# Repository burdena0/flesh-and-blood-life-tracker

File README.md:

# Flesh and Blood Life Tracker

A two-player life and resource counter for Flesh and Blood. This repo contains the compact E1 version: ESP32-S3 firmware, a KiCad carrier board, and host tests. It supports 20 or 40 starting life, undo, reset confirmation, and resource tracking. It can also serve as a general tabletop counter; no game artwork or logos are included.

## Current hardware and firmware

- ESP32-S3-Zero module, native ESP-IDF/FreeRTOS through PlatformIO.
- CL3641AH four-digit common-cathode display and SN74HC595 shift register.
- Debounced button events, state ownership, multiplexed display updates and resource LEDs.
- 70 x 80 mm two-layer KiCad carrier board with editable schematic, footprints and BOM.
- Host tests for game-state and shift-register behavior.

Read `README.txt` for the exact GPIO map, parts and assembly instructions. Build from
`firmware` with PlatformIO. Host test sources and CMake configuration are in
`firmware/tests`. The complete original workspace also contains historical Pico,
normal-ESP32 and older carrier variants; they are intentionally not mixed into this
current revision snapshot. Paths in historical prose may refer to those excluded
variants. Do not substitute their pin maps for the compact S3 board.

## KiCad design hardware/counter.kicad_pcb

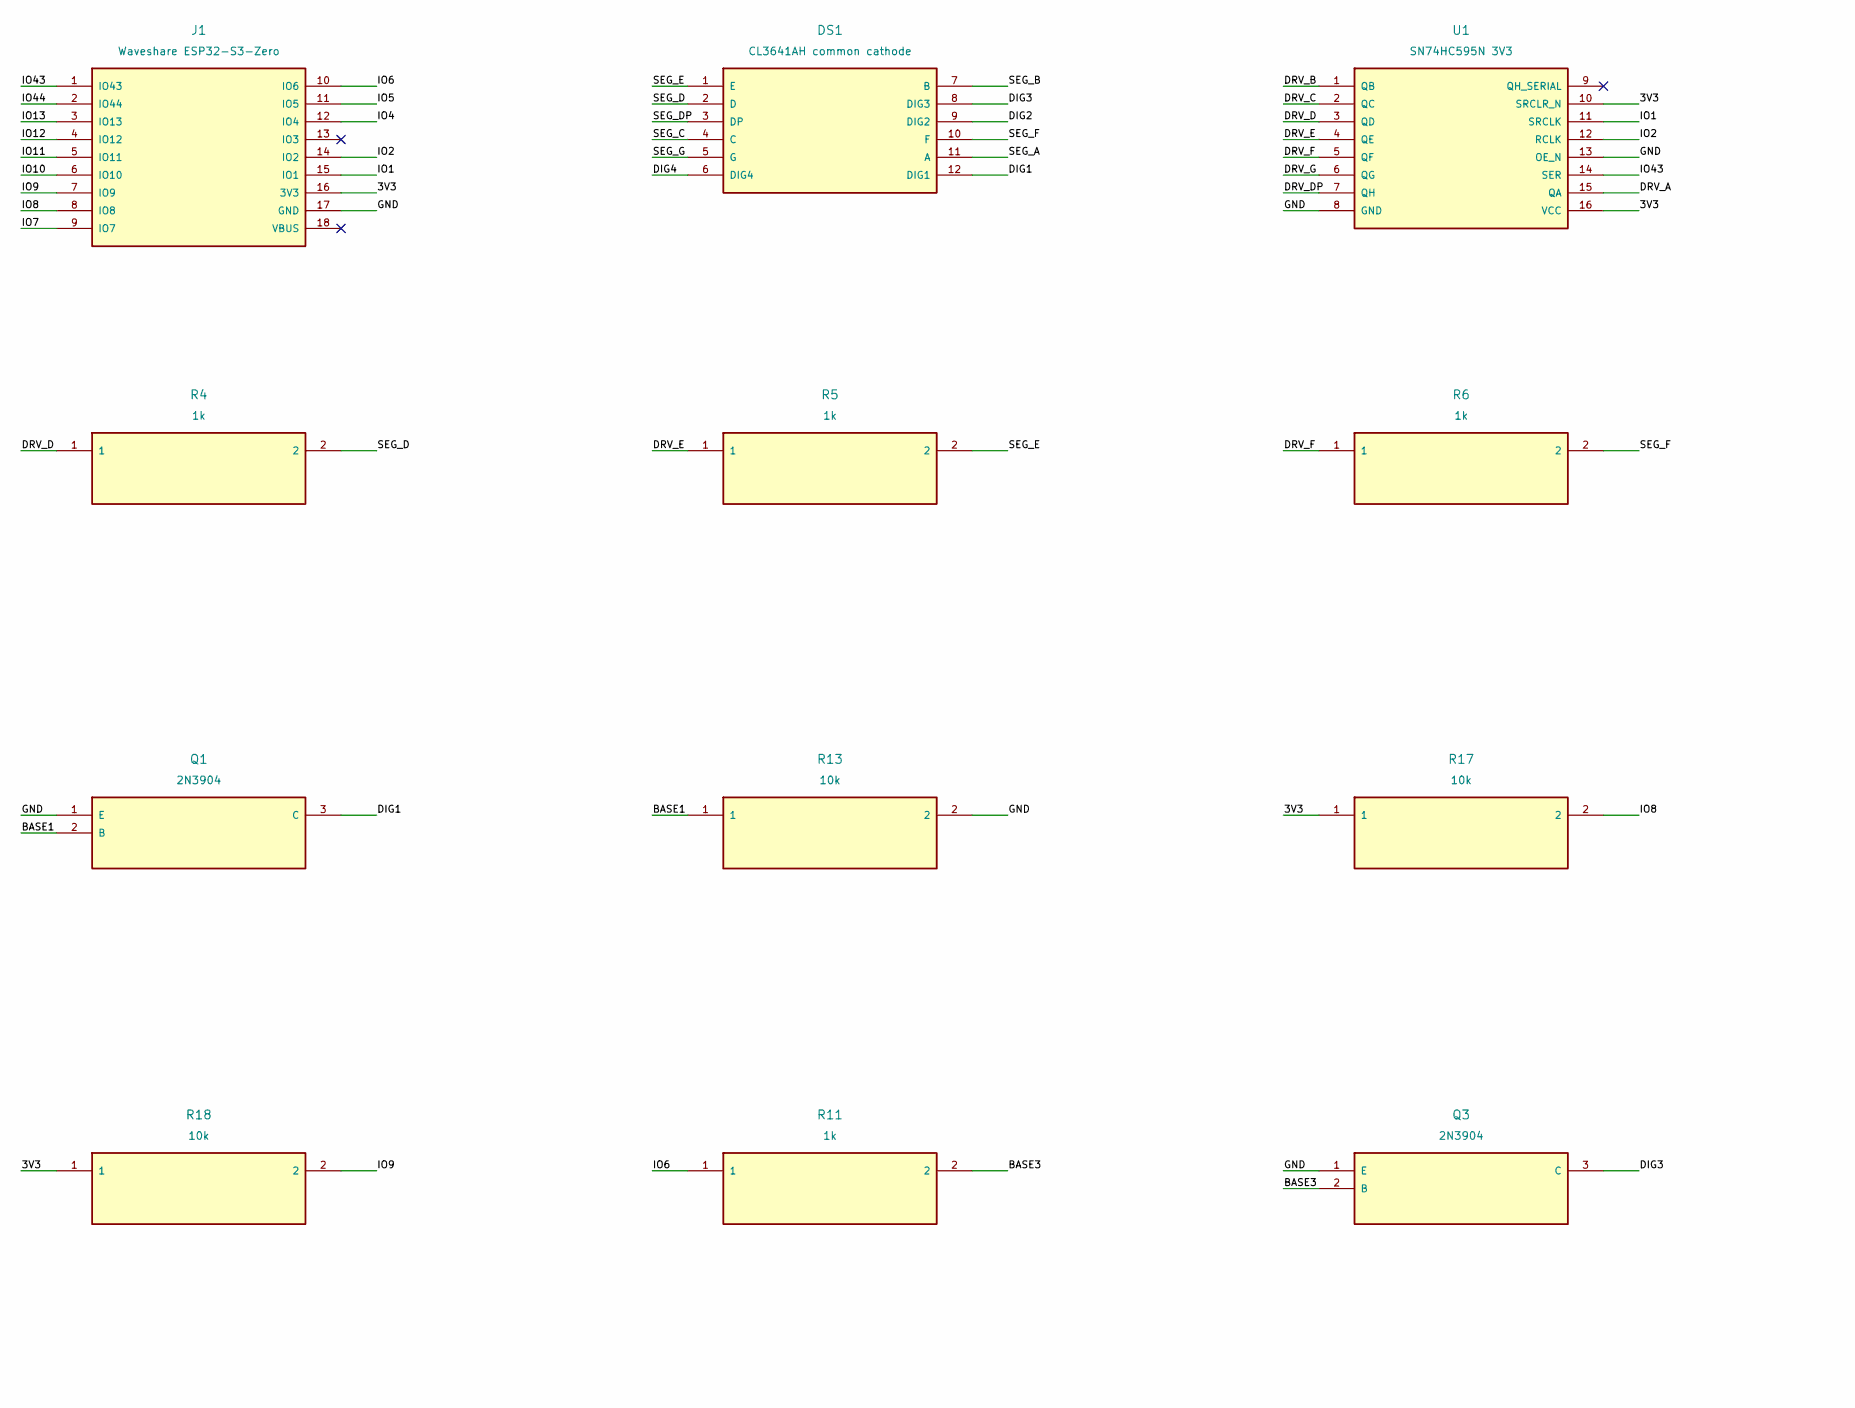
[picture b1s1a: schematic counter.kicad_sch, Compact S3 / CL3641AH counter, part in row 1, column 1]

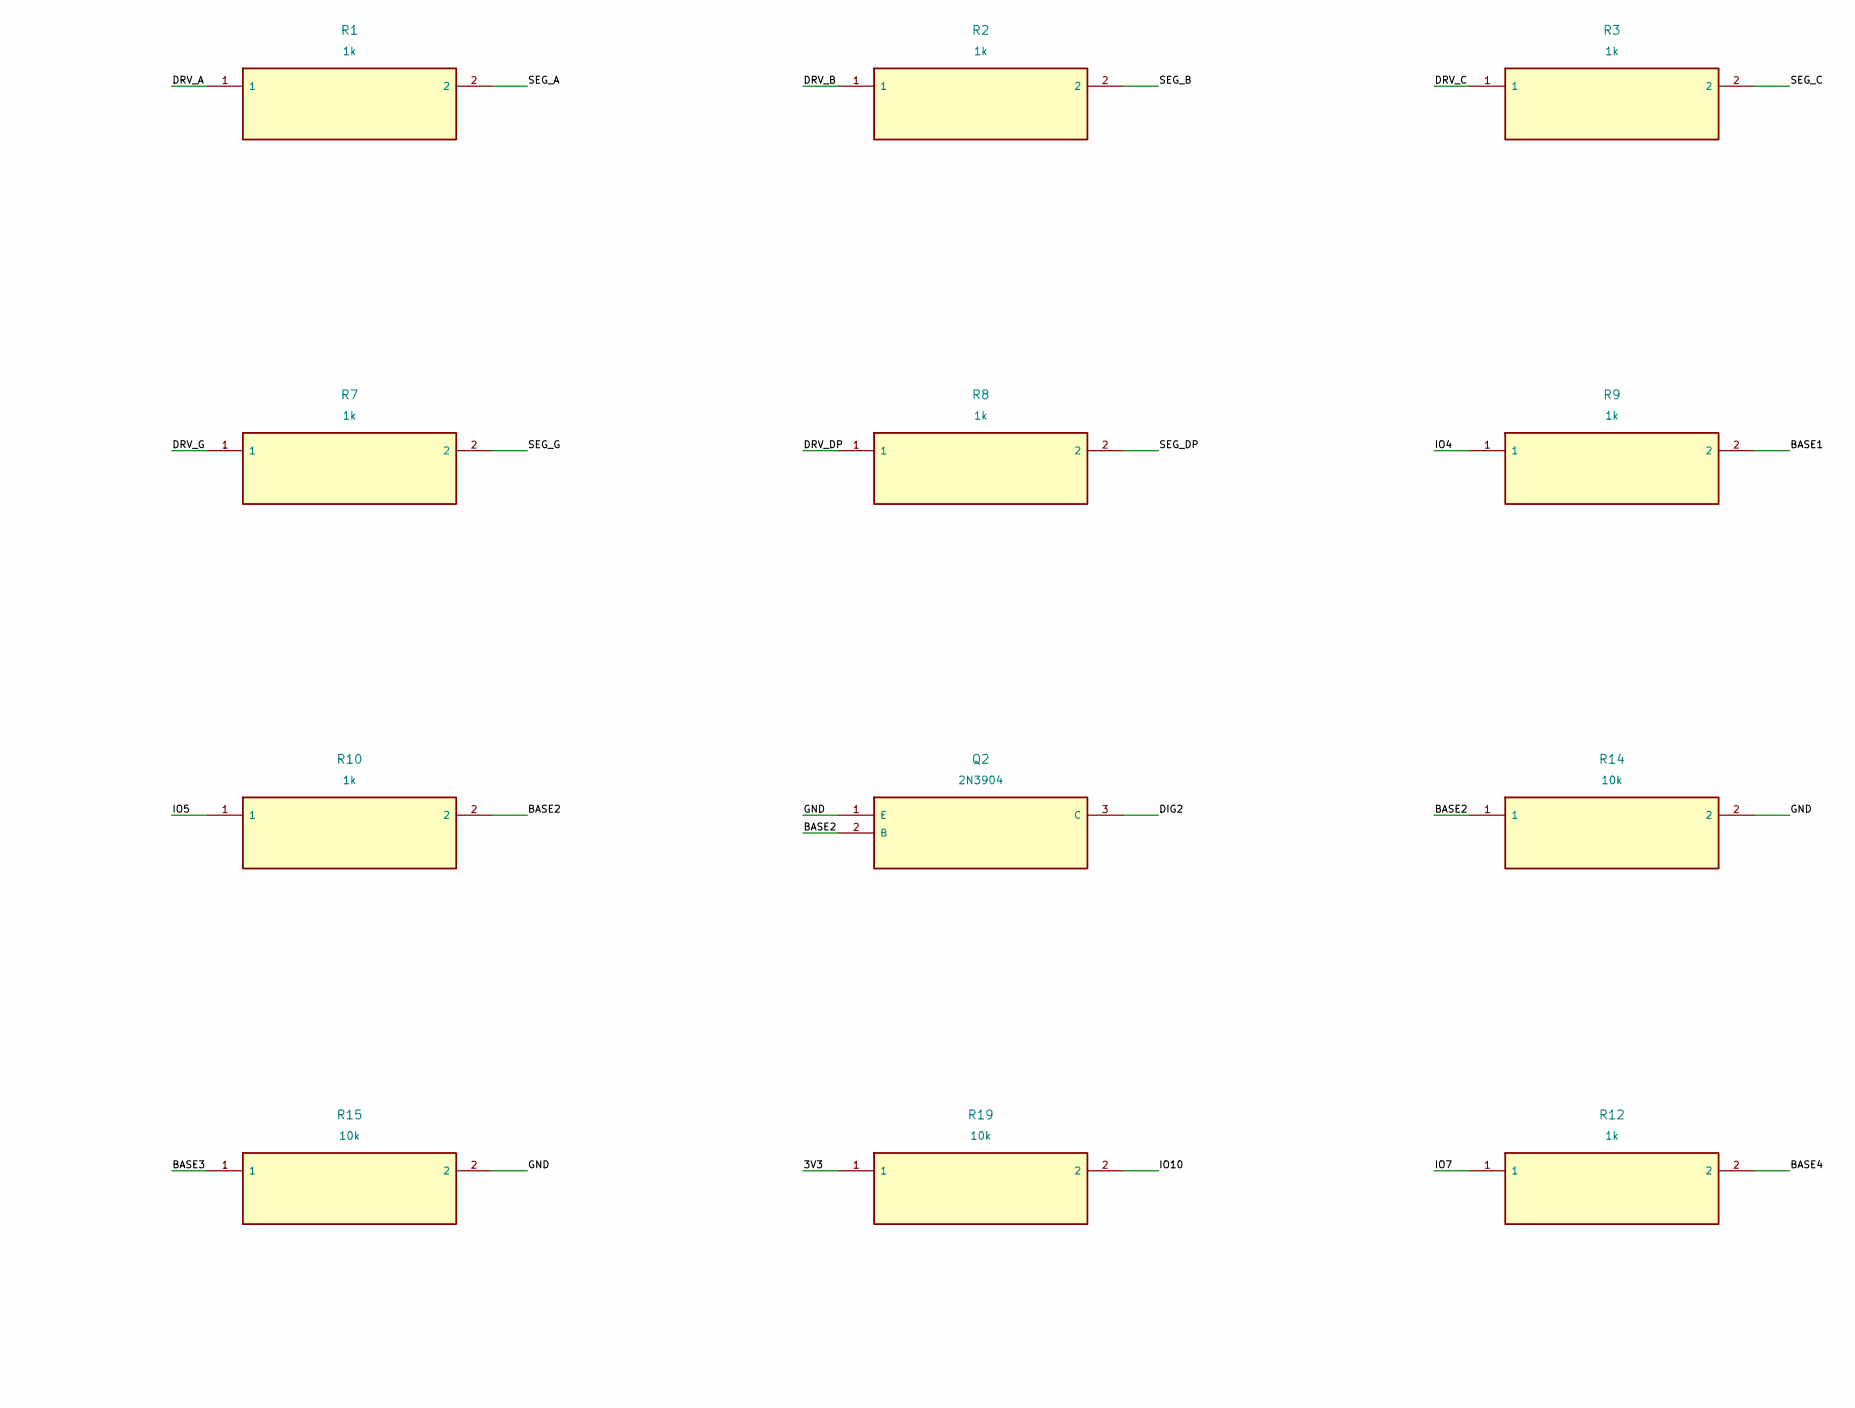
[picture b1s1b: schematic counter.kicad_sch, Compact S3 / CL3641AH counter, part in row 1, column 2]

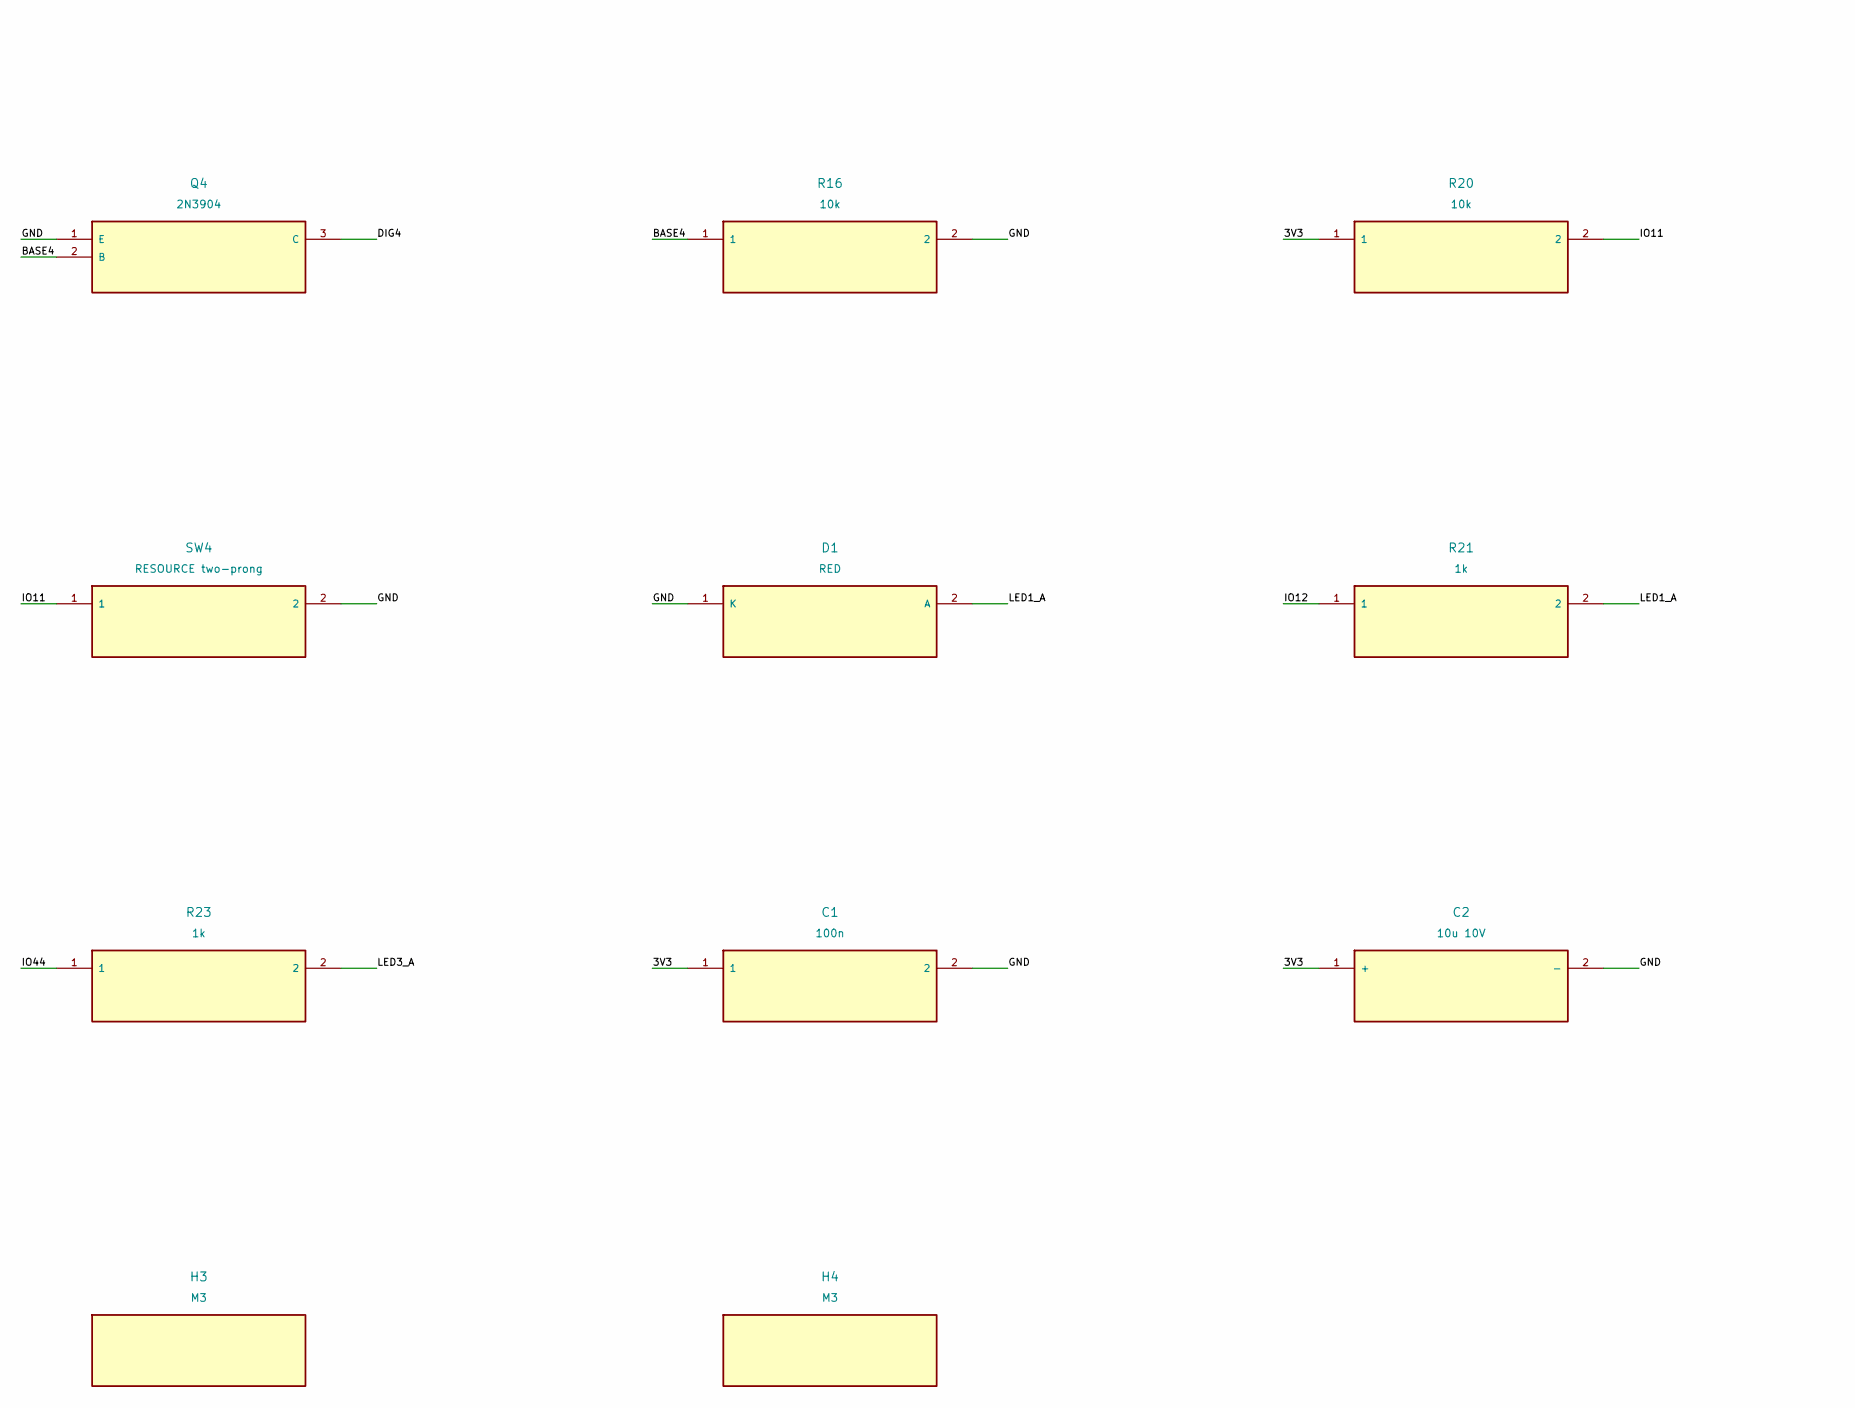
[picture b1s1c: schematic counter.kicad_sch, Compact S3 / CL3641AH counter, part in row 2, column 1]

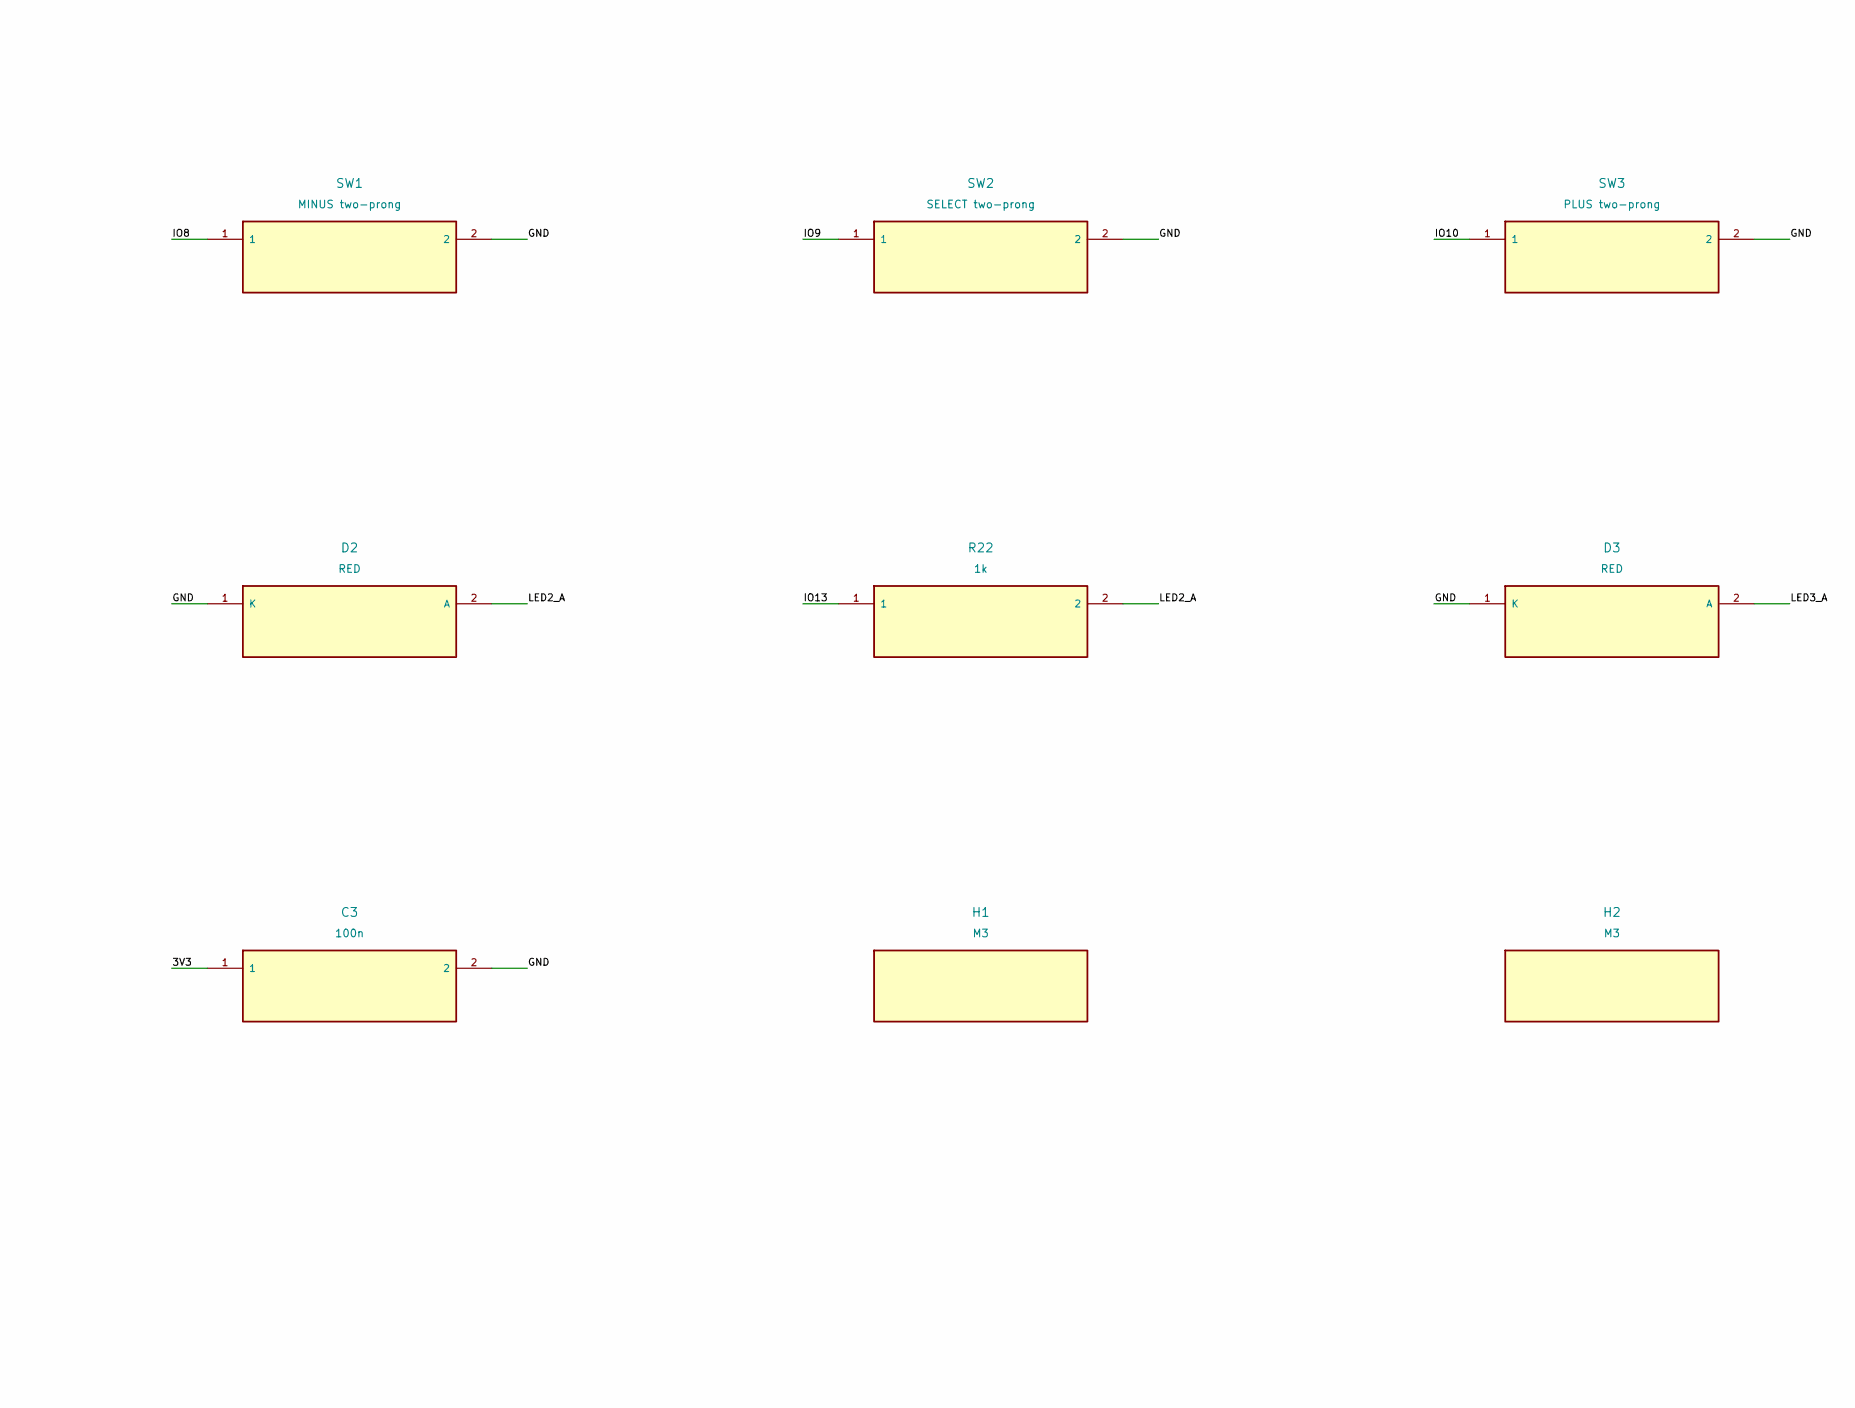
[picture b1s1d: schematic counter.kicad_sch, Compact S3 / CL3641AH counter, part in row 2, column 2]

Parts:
C1, C3: 100n; C_Disc_D5.0mm_W2.5mm_P5.00mm
C2: 10u 10V; CP_Radial_D5.0mm_P2.00mm
D1, D2, D3: RED; LED_D5.0mm
DS1: CL3641AH common cathode; CL3641AH_30x14_P2.54_R10.16
H1, H2, H3, H4: M3; MountingHole_3.2mm_M3
J1: Waveshare ESP32-S3-Zero; Waveshare_ESP32_S3_Zero_USB_Down
Q1, Q2, Q3, Q4: 2N3904; TO-92_Inline
R1, R2, R3, R4, R5, R6, R7, R8, R9, R10, R11, R12: 1k; R_Axial_DIN0207_L6.3mm_D2.5mm_P7.62mm_Horizontal
R13, R14, R15, R16, R17, R18, R19, R20: 10k; R_Axial_DIN0207_L6.3mm_D2.5mm_P7.62mm_Horizontal
R21, R22, R23: 1k; R_Axial_DIN0207_L6.3mm_D2.5mm_P2.54mm_Vertical
SW1: MINUS two-prong; Switch_2wire_2.54_or_5.08
SW2: SELECT two-prong; Switch_2wire_2.54_or_5.08
SW3: PLUS two-prong; Switch_2wire_2.54_or_5.08
SW4: RESOURCE two-prong; Switch_2wire_2.54_or_5.08
U1: SN74HC595N 3V3; DIP-16_W7.62mm

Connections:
/3V3: C1.1, C2.1 (+), C3.1, J1.16 (3V3), R17.1, R18.1, R19.1, R20.1, U1.10 (SRCLR_N), U1.16 (VCC)
/BASE1: Q1.2 (B), R9.2, R13.1
/BASE2: Q2.2 (B), R10.2, R14.1
/BASE3: Q3.2 (B), R11.2, R15.1
/BASE4: Q4.2 (B), R12.2, R16.1
/DIG1: DS1.12 (DIG1), Q1.3 (C)
/DIG2: DS1.9 (DIG2), Q2.3 (C)
/DIG3: DS1.8 (DIG3), Q3.3 (C)
/DIG4: DS1.6 (DIG4), Q4.3 (C)
/DRV_A: R1.1, U1.15 (QA)
/DRV_B: R2.1, U1.1 (QB)
/DRV_C: R3.1, U1.2 (QC)
/DRV_D: R4.1, U1.3 (QD)
/DRV_DP: R8.1, U1.7 (QH)
/DRV_E: R5.1, U1.4 (QE)
/DRV_F: R6.1, U1.5 (QF)
/DRV_G: R7.1, U1.6 (QG)
/GND: C1.2, C2.2 (-), C3.2, D1.1 (K), D2.1 (K), D3.1 (K), J1.17 (GND), Q1.1 (E), Q2.1 (E), Q3.1 (E), Q4.1 (E), R13.2, R14.2, R15.2, R16.2, SW1.2, SW2.2, SW3.2, SW4.2, U1.8 (GND), U1.13 (OE_N)
/IO1: J1.15 (IO1), U1.11 (SRCLK)
/IO2: J1.14 (IO2), U1.12 (RCLK)
/IO4: J1.12 (IO4), R9.1
/IO5: J1.11 (IO5), R10.1
/IO6: J1.10 (IO6), R11.1
/IO7: J1.9 (IO7), R12.1
/IO8: J1.8 (IO8), R17.2, SW1.1
/IO9: J1.7 (IO9), R18.2, SW2.1
/IO10: J1.6 (IO10), R19.2, SW3.1
/IO11: J1.5 (IO11), R20.2, SW4.1
/IO12: J1.4 (IO12), R21.1
/IO13: J1.3 (IO13), R22.1
/IO43: J1.1 (IO43), U1.14 (SER)
/IO44: J1.2 (IO44), R23.1
/LED1_A: D1.2 (A), R21.2
/LED2_A: D2.2 (A), R22.2
/LED3_A: D3.2 (A), R23.2
/SEG_A: DS1.11 (A), R1.2
/SEG_B: DS1.7 (B), R2.2
/SEG_C: DS1.4 (C), R3.2
/SEG_D: DS1.2 (D), R4.2
/SEG_DP: DS1.3 (DP), R8.2
/SEG_E: DS1.1 (E), R5.2
/SEG_F: DS1.10 (F), R6.2
/SEG_G: DS1.5 (G), R7.2

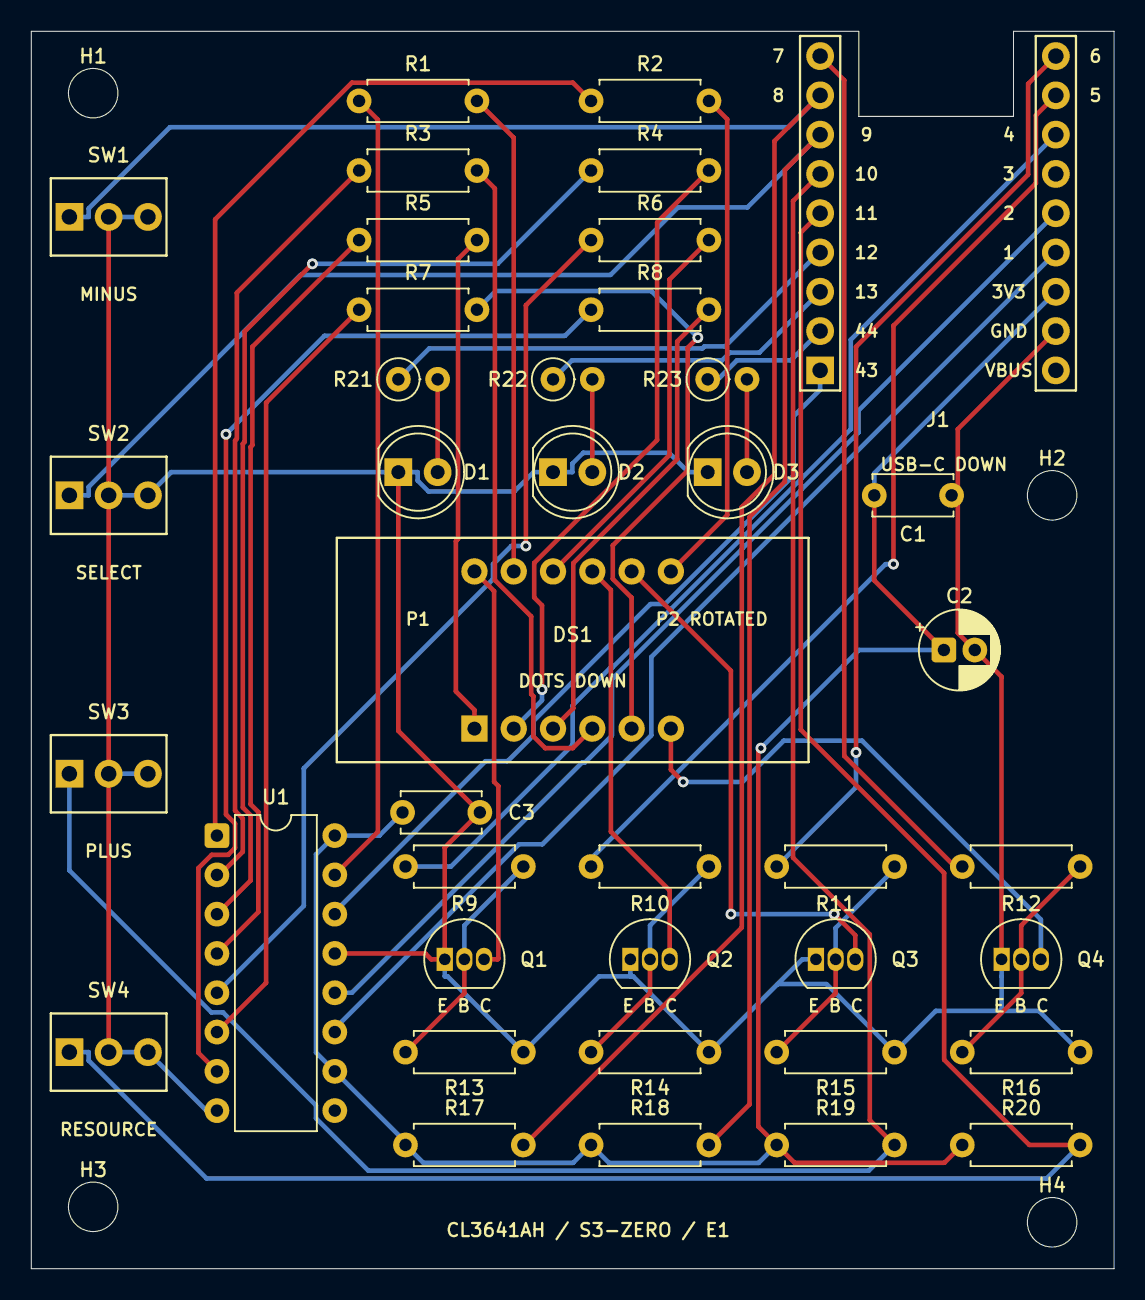
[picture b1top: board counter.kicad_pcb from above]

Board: 2 copper layers, 70.0 x 80.0 mm, 44 parts (0 on the bottom side), 43 nets.

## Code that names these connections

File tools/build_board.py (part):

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rect(f,-15.25,-7.25,15.25,7.25,p.F_SilkS)
rect(f,-15.5,-7.5,15.5,7.5,p.F_CrtYd,.05)
rect(f,-15,-7,15,7,p.F_Fab,.1);save_custom(f)
dpins={'11':'A','7':'B','4':'C','2':'D','1':'E','10':'F','5':'G','3':'DP','12':'DIG1','9':'DIG2','8':'DIG3','6':'DIG4'}
d=add('DS1','CL3641AH common cathode',f,(35,40),{n:'SEG_'+v if len(v)<3 else v for n,v in dpins.items()},dpins)
d.Reference().SetPosition(vec(35,39))
text('P1',25,38,.8);text('P2 ROTATED',44,38,.8);text('DOTS DOWN',35,42,.8)
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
